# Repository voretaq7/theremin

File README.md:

# theremin
A vacuum tube theremin using modern-production tubes

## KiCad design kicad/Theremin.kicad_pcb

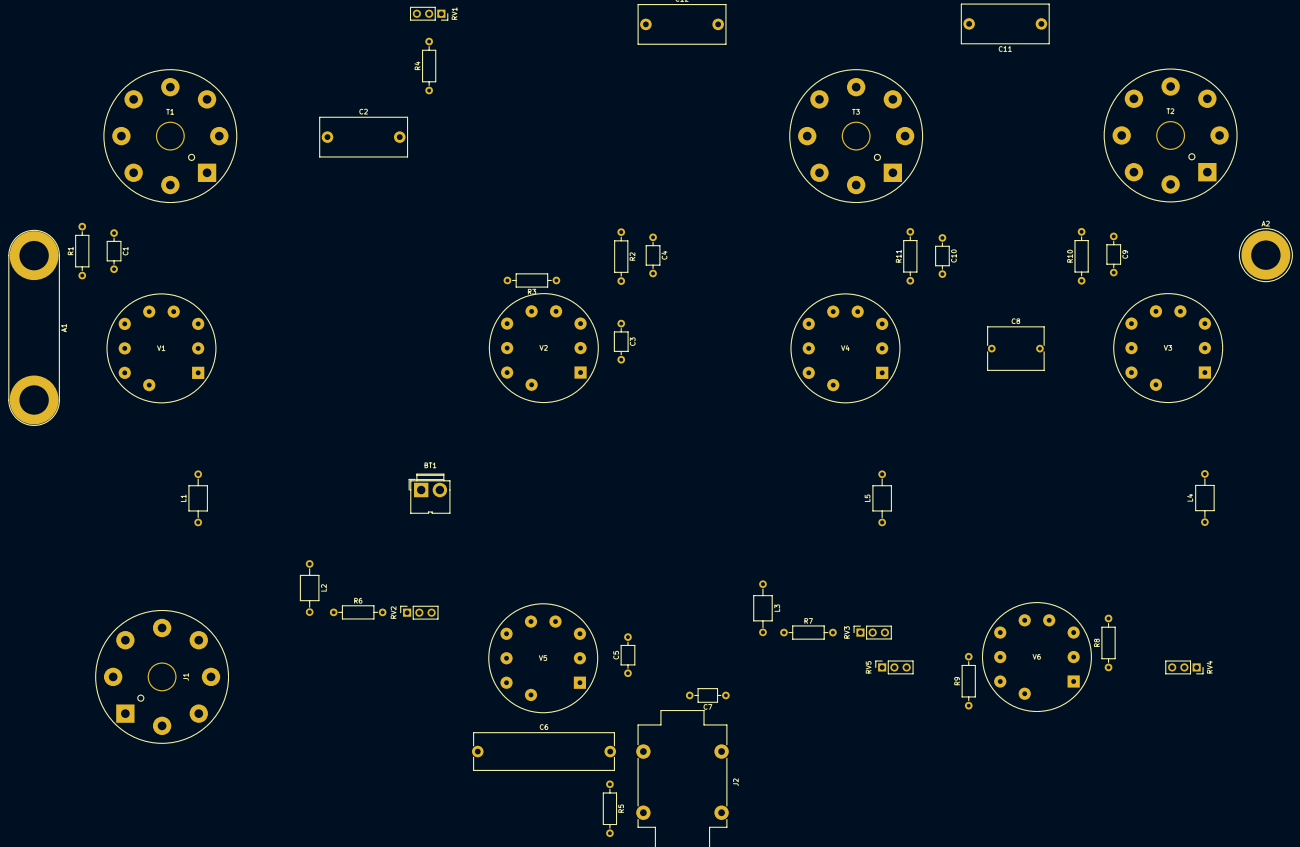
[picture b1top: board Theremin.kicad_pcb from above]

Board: 2 copper layers, 47 parts (0 on the bottom side), 36 nets, no tracks yet.

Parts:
A1: Volume_Antenna; Banana_Jack_2Pin
A2: Pitch_Antenna; Banana_Jack_1Pin
BT1: 9V Battery; JWT_A3963_1x02_P3.96mm_Vertical
C1, C9, C10: 50pF; C_Axial_L3.8mm_D2.6mm_P7.50mm_Horizontal
C2, C11, C12: 1-100pF; C_Rect_L18.0mm_W8.0mm_P15.00mm_FKS3_FKP3
C3: 500pF; C_Axial_L3.8mm_D2.6mm_P7.50mm_Horizontal
C4, C5: 250pF; C_Axial_L3.8mm_D2.6mm_P7.50mm_Horizontal
C6: 0.2uF; C_Rect_L29.0mm_W7.6mm_P27.50mm_MKT
C7: 100pF; C_Axial_L3.8mm_D2.6mm_P7.50mm_Horizontal
C8: 1-10pF; C_Rect_L11.5mm_W8.8mm_P10.00mm_MKT
J1: Power_Plug; Valve_Octal
J2: Audio Out; Jack_6.35mm_Neutrik_NMJ4HFD3_Horizontal
L1, L2, L3, L4, L5: L; L_Axial_L5.0mm_D3.6mm_P10.00mm_Horizontal_Murata_BL01RN1A2A2
R1, R10, R11: 1Meg; R_Axial_DIN0207_L6.3mm_D2.5mm_P10.16mm_Horizontal
R2, R4: 5K; R_Axial_DIN0207_L6.3mm_D2.5mm_P10.16mm_Horizontal
R3, R5, R8, R9: 1M; R_Axial_DIN0207_L6.3mm_D2.5mm_P10.16mm_Horizontal
R6, R7: 1K; R_Axial_DIN0207_L6.3mm_D2.5mm_P10.16mm_Horizontal
RV1: 1M; PinSocket_1x03_P2.54mm_Vertical
RV2, RV3: 100K; PinSocket_1x03_P2.54mm_Vertical
RV4: 25K; PinSocket_1x03_P2.54mm_Vertical
RV5: 50K; PinSocket_1x03_P2.54mm_Vertical
T1: Volume Tank; Valve_Octal
T2: VPO Tank; Valve_Octal
T3: FPO Tank; Valve_Octal
V1, V2, V3, V4: ECC83; Valve_Noval_P
V5, V6: EF86; Valve_Noval_P

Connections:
B+1: J1.6, J1.7, L1.1, L4.1, L5.1
B+2: J1.2, J1.3, L2.1, L3.1
C: BT1.2, RV1.3
GND: BT1.1, C2.2, C3.2, C4.2, C5.2, C11.2, C12.2, J1.1, J1.8, J2.S, J2.SN, R3.1, R5.2, R8.2, R9.2, T1.1, T1.2, T2.1, T2.2, T3.1, T3.2, V5.3, V5.7, V5.8, V6.3, V6.7
unnamed: A1.1, T1.4, V1.3, V1.8
unnamed: A1.2, V2.1, V2.2, V2.8
unnamed: A2.1, C9.1, C11.1, R10.2, T2.7, T2.8
unnamed: C1.1, C2.1, R1.2, T1.7, T1.8
unnamed: C1.2, R1.1, V1.2, V1.7
unnamed: C3.1, R2.2, V2.3
unnamed: C4.1, R2.1, RV1.1
unnamed: C5.1, R4.1, V5.1
unnamed: C6.1, RV2.2
unnamed: C6.2, J2.T, J2.TN, R5.1
unnamed: C7.1, RV3.2
unnamed: C7.2, V5.9
unnamed: C8.1, C9.2, R10.1, V3.2, V3.7
unnamed: C10.1, C12.1, R11.2, T3.7, T3.8
unnamed: C8.2, C10.2, R11.1, V4.2, V4.7
unnamed: J1.4, V1.4, V1.5, V2.4, V2.5, V3.4, V3.5, V4.4, V4.5, V5.4, V6.4
unnamed: J1.5, V1.9, V2.9, V3.9, V4.9, V5.5, V6.5
unnamed: L1.2, V1.1, V1.6
unnamed: L2.2, R6.1
unnamed: L3.2, R7.1
unnamed: L4.2, V3.1, V3.6
unnamed: L5.2, V4.1, V4.6
unnamed: R3.2, V2.6, V2.7
unnamed: R4.2, RV1.2
unnamed: R6.2, RV2.1
unnamed: R7.2, RV3.1
unnamed: R8.1, RV4.3, V6.1
unnamed: R9.1, RV5.3, V6.9
unnamed: RV2.3, V5.6
unnamed: RV3.3, V6.6, V6.8
unnamed: RV4.1, RV4.2, T2.5, V3.3, V3.8
unnamed: RV5.1, RV5.2, T3.5, V4.3, V4.8

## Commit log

2018-12-18 Initial Commit: Theremin circuit schematics & proposed chassis layouts
2018-12-30 Assembly Prep Changes
    - Modified instrument layout to reflect use of series RC filter for VO output
    - Split power supply & added octal base diagrams to instrument & PSU Schematic
    - Added Bill of Materials (BOM.txt)
2018-12-31 Clean up Power Supply schematic ; Move heaters to Instrument chassis.
    - Removed stray instrument components from PSU schematic
    - Moved heaters to Instrument chassis schematic & connect to power socket
    - Added Standby/On Switch to BOM
    - Added pilot lamp components to BOM
2019-01-24 Change PCB style output jack for solder lug style jack
2019-01-26 Updated schematic & layout with notes from Rockmore & Rosen units
    Power Supply:
    - Filtering with 100 ohm resistors.
    This will produce HV B+ that may need reducing in the
    instrument chassis.
    Instrument:
    - Misc. Cleanups to schematic
2019-01-26 Cleanup Commit
2019-01-26 Add 3D Printed insulator collars for C-V100P
2019-02-02 Add diagram of 8-pin tank module
    Pin 1 ---- Capacitor
    Pin 2 ---- Coil Start
    Pin 3 ---- Coil Tap: 10%
    Pin 4 ---- Coil Tap: 25%
    Pin 5 ---- Coil Tap: 33%
    Pin 6 ---- Coil Tap: 50%
2019-02-23 Add RF shields for FPO & VPO
    Two RF shields are required to prevent excessive coupling of the oscillators
    due to their proximity. These can be any suitable grounded metal shield.
    The shield need not extend past the oscillator tubes (most coupling is at
    the coils) however this was done to prevent tube-to-tube RF coupling.
    Due to proximity to the oscillator coils the sheilds must be rigid
    (movement will affect oscillator frequency & amplitude through capacitive
2019-03-01 Add connections for pitch oscillators
    - Tank to oscillator driver: 50pf / 1Meg ohm, grid leak through
    coil.
    - Tank to Mixer: Tap off cathode, 100pf isolating cap.
    Construction Note: Mixer grid leak resistors connect to cathode.
    Mixer tube is biased beyond cutoff by negative voltage from
    the oscillator tubes.
2019-03-02 Add Construction & Design note files.
    - Construction Notes includes specific advice on the physical assembly
    of the theremin (component locations, layout, etc.)
    - Design Notes includes the rationale behind certain design choices.
2019-03-02 Update instrument schematic with chokes & cap/resistor values
    - Added RF chokes to plate supplies of mixer tube & all oscillator tubes
    This greatly improves waveform shape and gives better filtering than using
    resistors in the plate supplies.
    - Added feedback capacitors & grid leak resistors for pitch oscillator tanks
    Values should be suitable for 12AX7, 12AY7, 12AT7 or 12AU7 tubes operating
    at 170-185KHz. Higher frequencies should also work.
2019-11-29 Fall 2019 Update - Pitch section design complete & verified
    BOM: Minor updates, this BOM is incomplete & will be updated.
    Instrument layout & schematics reflowed to put volume loop on
    the left side.
2020-03-10 Add 1Meg bleeder resistor to power supply (B+2)
2020-03-10 Update instrument schematic with final volume control design
    Volume circuit layout should be pretty much finalized.
    Requires external 9V power supply for C- bias
2021-04-10 Update schematics & notes on volume circuit
    Implements a zero-current volume circuit that has been tested
    and provides good dynamics.
2021-04-10 Move Graffle files to Graffle dir & add KiCad schematic/layout
    Decided to sharpen my KiCad skills with this project.
    At the moment both the KiCad and Graffle version of the schematic
    are being kept in sync, but this will likely become a KiCad
    project.
